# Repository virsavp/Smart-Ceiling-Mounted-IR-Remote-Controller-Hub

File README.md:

Universal Remote Controller Hub

📂 Jump to Files:

🔧 Hardware (schematics & PCB)
💻 Firmware Code (coming soon)

This project is a compact, ceiling-mountable, smart IR controller hub based on the ESP32-S3-WROOM. 
It enables universal control of IR-based appliances like TVs, air conditioners, and fans using web UI, OTA, and automation features.

✨ Features

🔁 360° IR transmission with 10× TSAL6200 high-power IR LEDs
🔍 IR learning using TSOP38238 receiver
📡 Wi-Fi OTA updates + USB flashing via BOOT jumper
🌡️ DS18B20 temperature sensor (for fan/AC automation)
🔊 Optional WS2812 RGB LED status indicator
🖥️ Optional OLED display via JST I²C header (GPIO17/18)
🔘 Single config/setup button (GPIO2, safe boot compliant)
💾 External SPI flash (W25Q256JV) for IR code storage
🔌 USB-C power + LiPo battery with TP4056 charge module
🧲 Magnetic ceiling-mount enclosure with transparent IR window and venting

🧱 Hardware Overview	
	
Component	Details
MCU	- ESP32-S3 WROOM
IR TX	- 10× TSAL6200 + 2N2222 transistor driver
IR RX	- TSOP38238
Temp Sensor	- DS18B20 (GPIO10)
OLED Display	- SSD1306 via I²C (GPIO17=SDA, GPIO18=SCL)
RGB LED	- WS2812-2020 (GPIO16)
Button	- Config input on GPIO2 (1k pull-up)
External Flash	- W25Q256JV (CS: GPIO13, CLK: GPIO15, MOSI: GPIO5, MISO: GPIO4)
Power Input	- USB-C + LiPo via TP4056
Regulator	- AMS1117-3.3

📁 Repository Structure

/hardware/         → KiCad schematics, PCB files (licensed under CERN-OHL-S)
/3d_model/         → Enclosure STL or CAD (licensed under CC BY-SA 4.0)
/code/             → ESP32 firmware (to be added after layout)
LICENSE            → Dual license for hardware and enclosure
README.md          → This file

🧾 License

🔧 Schematics & PCB Design: CERN-OHL-S v2

🚧 Development Status

✅ Hardware design complete✅ PCB layout and routing complete🔲 Firmware development starts after placement confirmation

🙌 Contributions

Feel free to fork, improve, or repurpose this design. If you build upon it, keep it open-source under the same licenses.
For issues or suggestions, please open a GitHub issue or contact the maintainer.

Made with ❤️ by Vishnu – Electronics Hobbyist | KiCad Enthusiast | Open Hardware Advocate

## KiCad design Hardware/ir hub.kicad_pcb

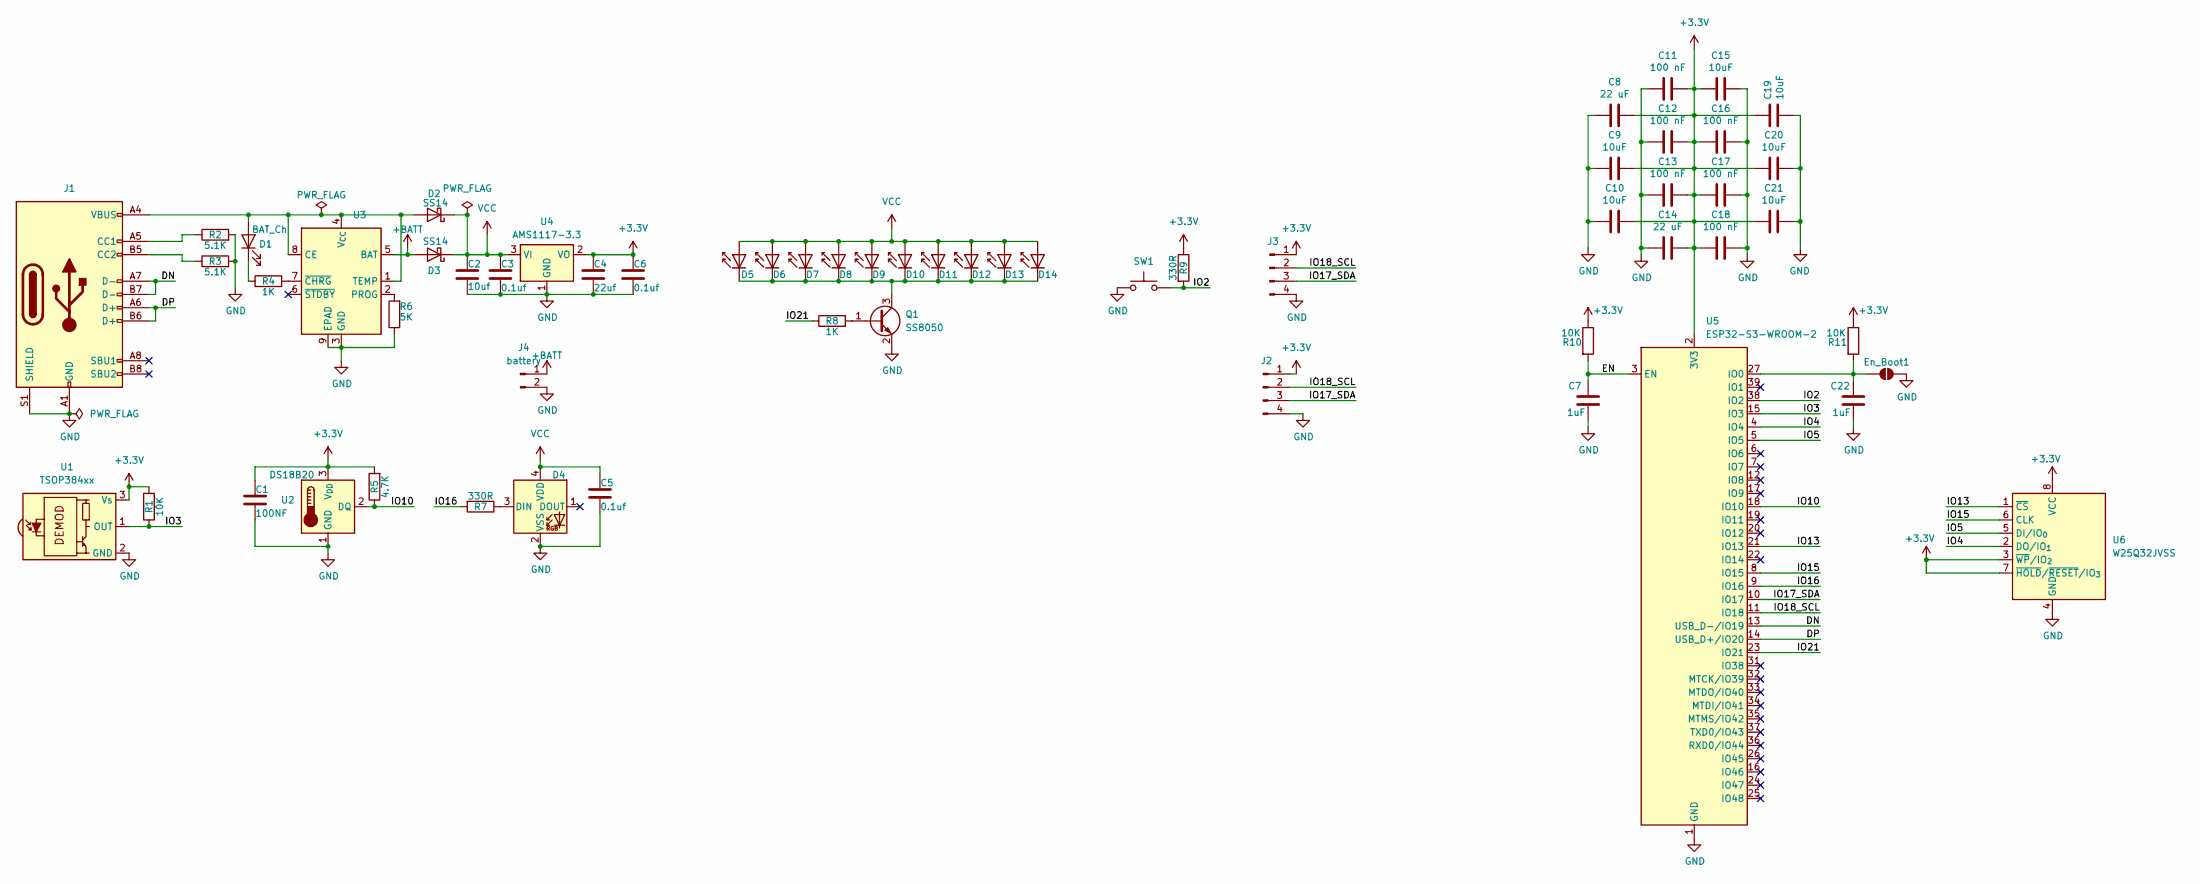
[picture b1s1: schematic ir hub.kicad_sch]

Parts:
C1: 100NF; C_0402_1005Metric
C2: 10uf; C_0805_2012Metric
C3, C5, C6: 0.1uf; C_0402_1005Metric
C4: 22uf; C_0805_2012Metric
C7, C22: 1uF; C_0402_1005Metric; LCSC C52923
C8, C14: 22 uF; C_0603_1608Metric; LCSC C59461
C9, C10, C15, C21: 10uF; C_0402_1005Metric; LCSC C15525
C11, C12, C13, C16, C17, C18: 100 nF; C_0402_1005Metric; LCSC C1525
C19, C20: 10uF; C_0603_1608Metric; LCSC C19702
D1: BAT_Ch; LED_0201_0603Metric
D2, D3: SS14; D_SMA
D4: WS2812B-2020; LED-SMD_4P-L2.0-W2.0-TL_WS2812B-2020
D5, D6, D7, D8, D9, D10, D11, D12, D13, D14: TSAL4400; LED_D3.0mm_IRBlack
En_Boot1: SolderJumper_2_Open; SolderJumper-2_P1.3mm_Open_RoundedPad1.0x1.5mm
J1: USB_C_Receptacle_USB2.0_16P; USB_C_Receptacle_GCT_USB4110
J2: I2C EXPANSION; JST_PH_S4B-PH-K_1x04_P2.00mm_Horizontal
J3: OLED DSP; JST_PH_S4B-PH-K_1x04_P2.00mm_Horizontal
J4: battery; JST_PH_B2B-PH-K_1x02_P2.00mm_Vertical
Q1: SS8050; SOT-23
R1, R10, R11: 10K; R_0402_1005Metric
R2, R3: 5.1K; R_0402_1005Metric
R4, R8: 1K; R_0402_1005Metric
R5: 4.7K; R_0402_1005Metric
R6: 5K; R_0402_1005Metric
R7, R9: 330R; R_0402_1005Metric
SW1: BTN; SW_Tactile_SPST_Angled_PTS645Vx83-2LFS
U1: TSOP384xx; Vishay_MINICAST-3Pin
U2: DS18B20; TO-92_Inline
U3: TP4056-42-ESOP8; SOIC-8-1EP_3.9x4.9mm_P1.27mm_EP2.41x3.3mm_ThermalVias
U4: AMS1117-3.3; SOT-223-3_TabPin2
U5: ESP32-S3-WROOM-2; ESP32-S3-WROOM-1U
U6: W25Q32JVSS; SOIC-8_5.3x5.3mm_P1.27mm

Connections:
+3.3V: C1.1, C4.1, C6.1, C8.1, C9.1, C10.1, C11.1, C12.1, C13.1, C14.1, C15.2, C16.2, C17.2, C18.2, C19.1, C20.2, C21.2, J2.1, J3.1, R1.2, R5.2, R9.1, R10.1, R11.1, U1.3 (Vs), U2.3 (V_{DD}), U4.2 (VO), U5.2 (3V3), U6.3 (~WP/IO_{2}), U6.7 (~HOLD/~RESET/IO_{3}), U6.8 (VCC)
+BATT: D3.2 (A), J4.1, U3.5 (BAT)
/DN: J1.A7 (D-), J1.B7 (D-), U5.13 (USB_D-/IO19)
/DP: J1.A6 (D+), J1.B6 (D+), U5.14 (USB_D+/IO20)
/EN: C7.1, R10.2, U5.3 (EN)
/IO2: R9.2, SW1.2, U5.38 (IO2)
/IO3: R1.1, U1.1 (OUT), U5.15 (IO3)
/IO4: U5.4 (IO4), U6.2 (DO/IO_{1})
/IO5: U5.5 (IO5), U6.5 (DI/IO_{0})
/IO10: R5.1, U2.2 (DQ), U5.18 (IO10)
/IO13: U5.21 (IO13), U6.1 (~CS)
/IO15: U5.8 (IO15), U6.6 (CLK)
/IO16: R7.2, U5.9 (IO16)
/IO17_SDA: J2.3, J3.3, U5.10 (IO17)
/IO18_SCL: J2.2, J3.2, U5.11 (IO18)
/IO21: R8.1, U5.23 (IO21)
GND: C1.2, C2.2, C3.2, C4.2, C5.2, C6.2, C7.2, C8.2, C9.2, C10.2, C11.2, C12.2, C13.2, C14.2, C15.1, C16.1, C17.1, C18.1, C19.2, C20.1, C21.1, C22.2, D4.2 (VSS), En_Boot1.2 (B), J1.A1 (GND), J1.A12 (GND), J1.B1 (GND), J1.B12 (GND), J1.S1 (SHIELD), J2.4, J3.4, J4.2, Q1.2 (E), R2.2, R3.2, R6.1, SW1.1, U1.2 (GND), U2.1 (GND), U3.3 (GND), U3.9 (EPAD), U4.1 (GND), U5.1 (GND), U5.40 (GND), U5.41 (GND), U6.4 (GND); also elsewhere on the board
unnamed: D1.2 (A), D2.2 (A), J1.A4 (VBUS), J1.A9 (VBUS), J1.B4 (VBUS), J1.B9 (VBUS), U3.1 (TEMP), U3.4 (V_{CC}), U3.8 (CE)
unnamed: D1.1 (K), R4.1
unnamed: D4.3 (DIN), R7.1
unnamed: D5.1 (K), D6.1 (K), D7.1 (K), D8.1 (K), D9.1 (K), D10.1 (K), D11.1 (K), D12.1 (K), D13.1 (K), D14.1 (K), Q1.3 (C)
unnamed 21: C22.1, En_Boot1.1 (A), R11.2, U5.27 (IO0); also elsewhere on the board
unnamed: J1.A5 (CC1), R2.1
unnamed: J1.B5 (CC2), R3.1
unnamed: Q1.1 (B), R8.2
unnamed: R6.2, U3.2 (PROG)
unnamed: R4.2, U3.7 (~CHRG)
VCC: C2.1, C3.1, C5.1, D2.1 (K), D3.1 (K), D4.4 (VDD), D5.2 (A), D6.2 (A), D7.2 (A), D8.2 (A), D9.2 (A), D10.2 (A), D11.2 (A), D12.2 (A), D13.2 (A), D14.2 (A), U4.3 (VI)

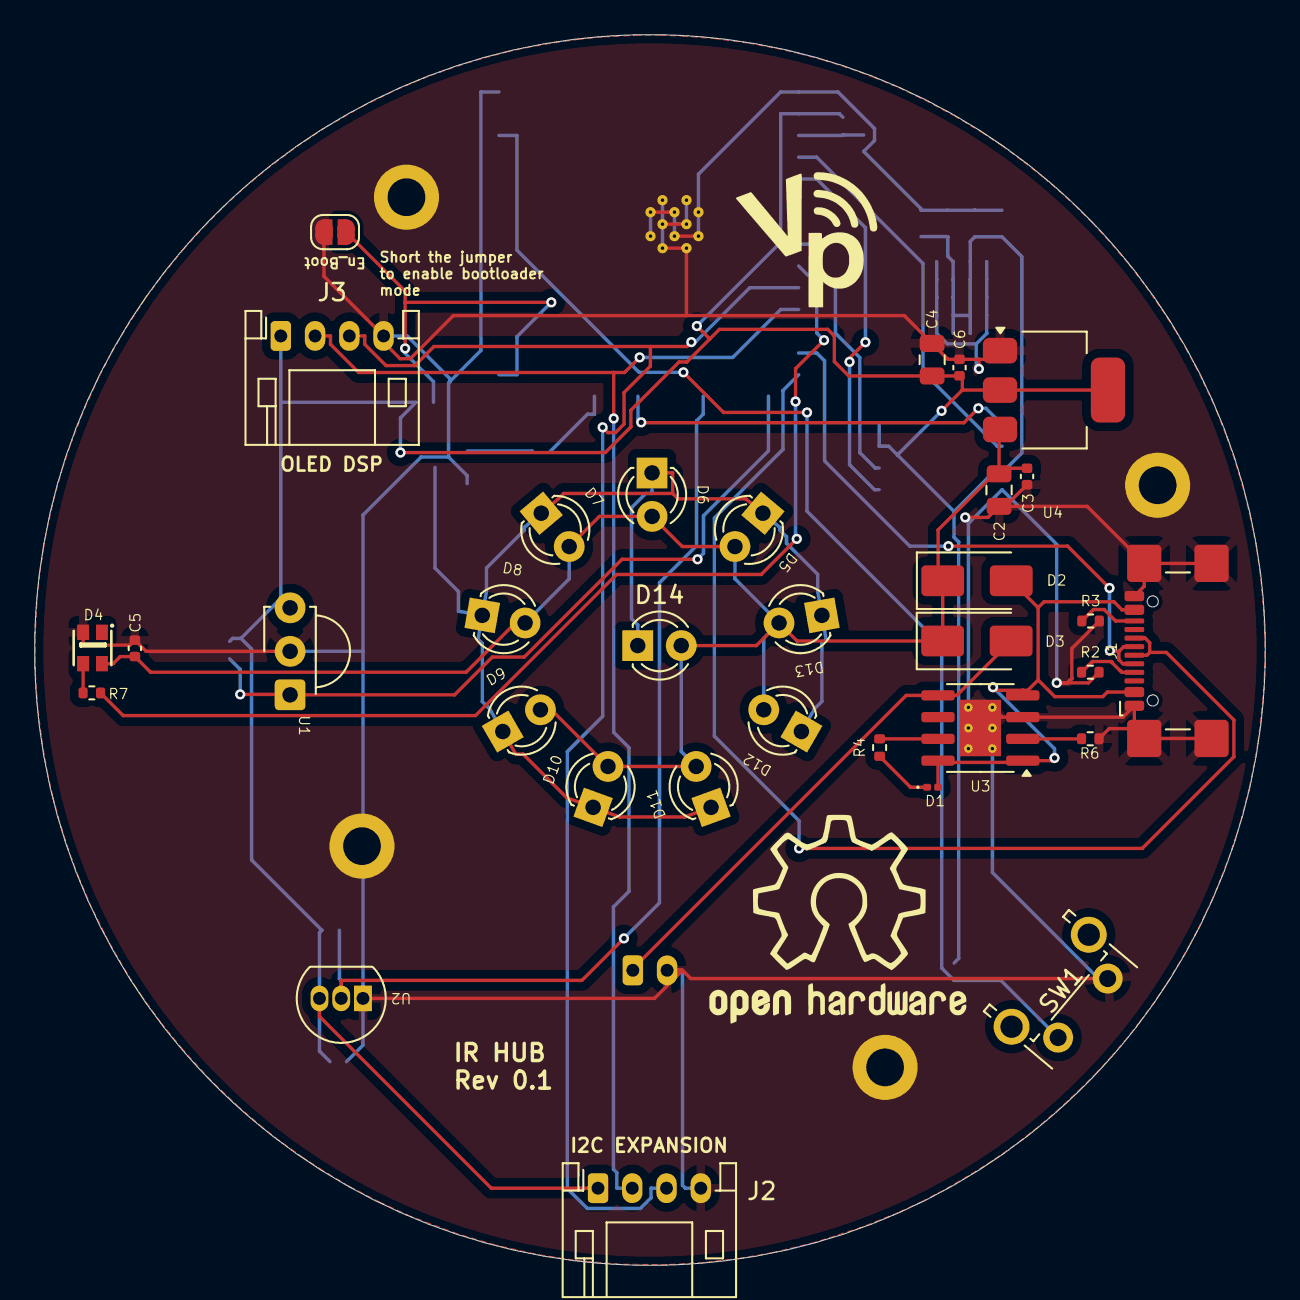
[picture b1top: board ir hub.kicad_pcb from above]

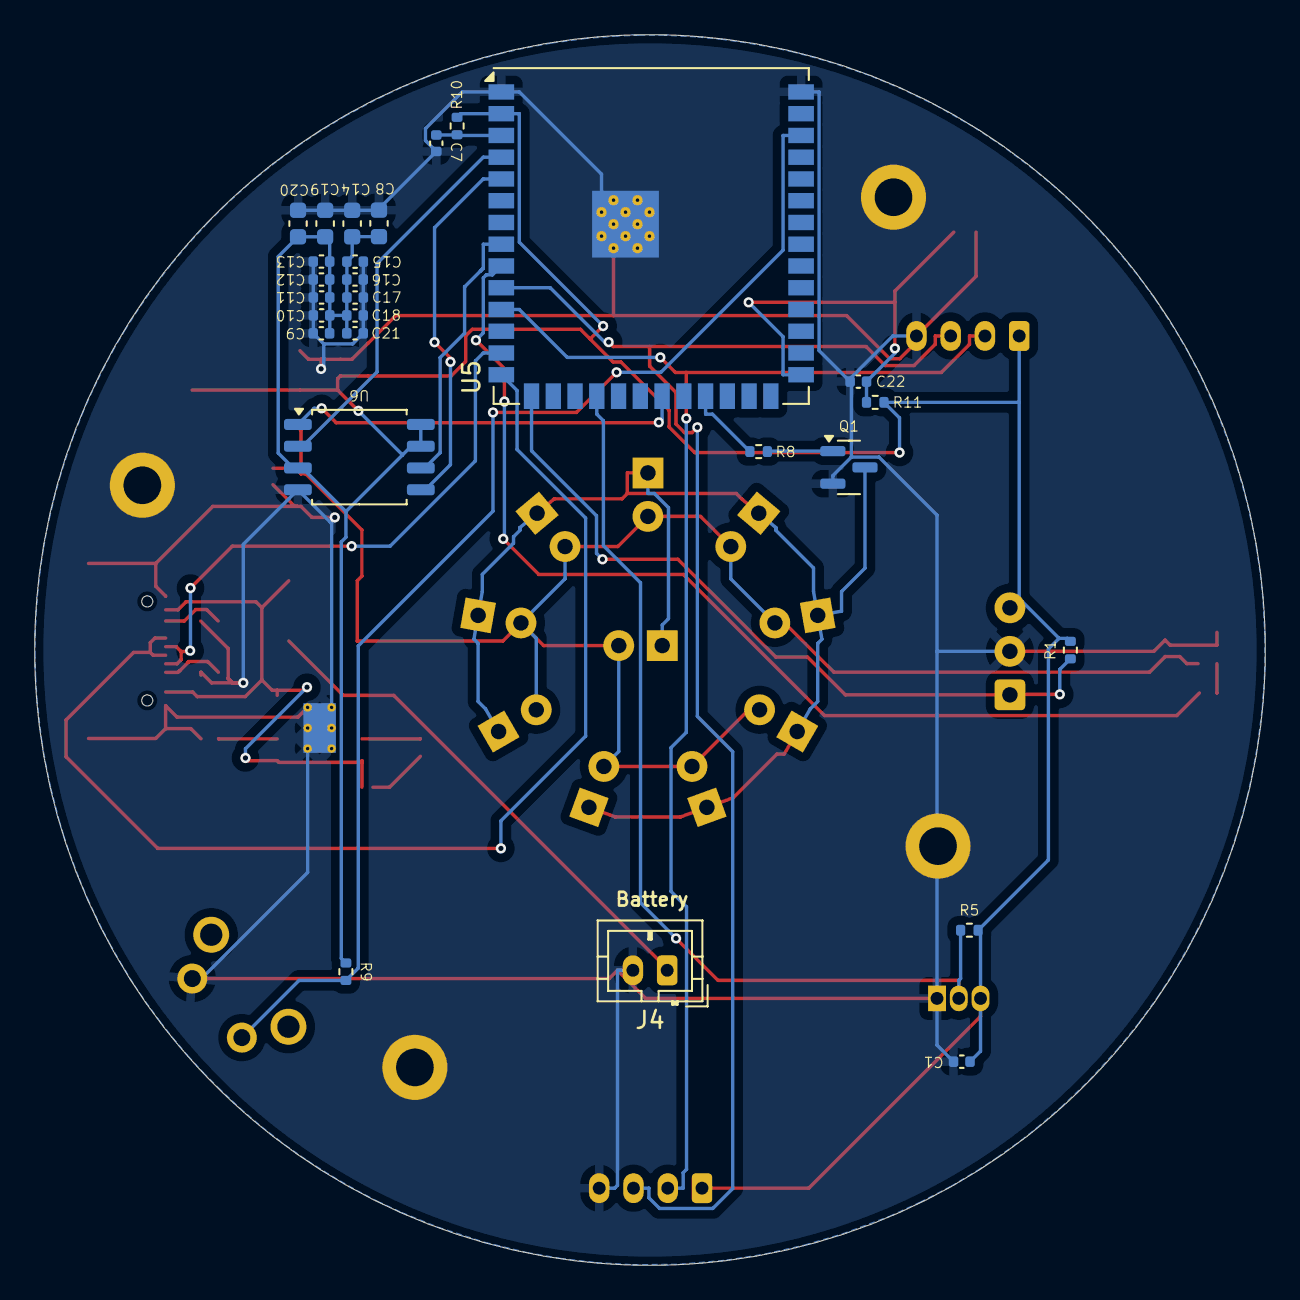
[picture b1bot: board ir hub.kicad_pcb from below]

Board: 2 copper layers, 71.8 x 71.8 mm, 60 parts (27 on the bottom side), 28 nets.

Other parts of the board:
En_Boot: SolderJumper_2_Open; SolderJumper-2_P1.3mm_Open_RoundedPad1.0x1.5mm

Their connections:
GND: En_Boot.2 (B); also elsewhere on the board
unnamed 21: En_Boot.1 (A); also elsewhere on the board

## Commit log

2025-06-14 Create LICENSE
2025-06-14 README.md
